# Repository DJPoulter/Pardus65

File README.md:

# Pardus65
Attempting to build a 65% keyboard from scratch

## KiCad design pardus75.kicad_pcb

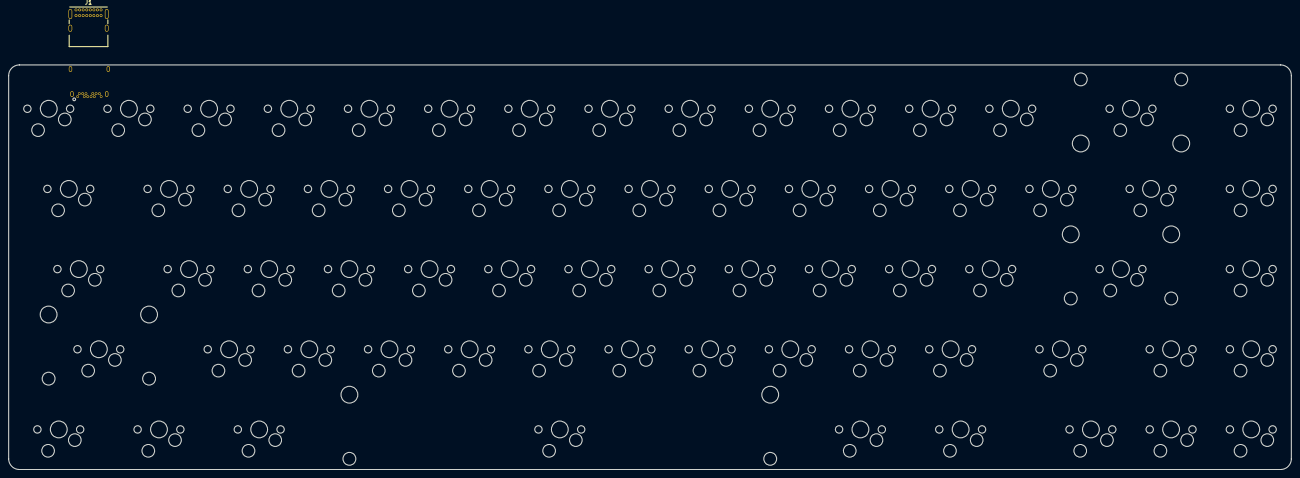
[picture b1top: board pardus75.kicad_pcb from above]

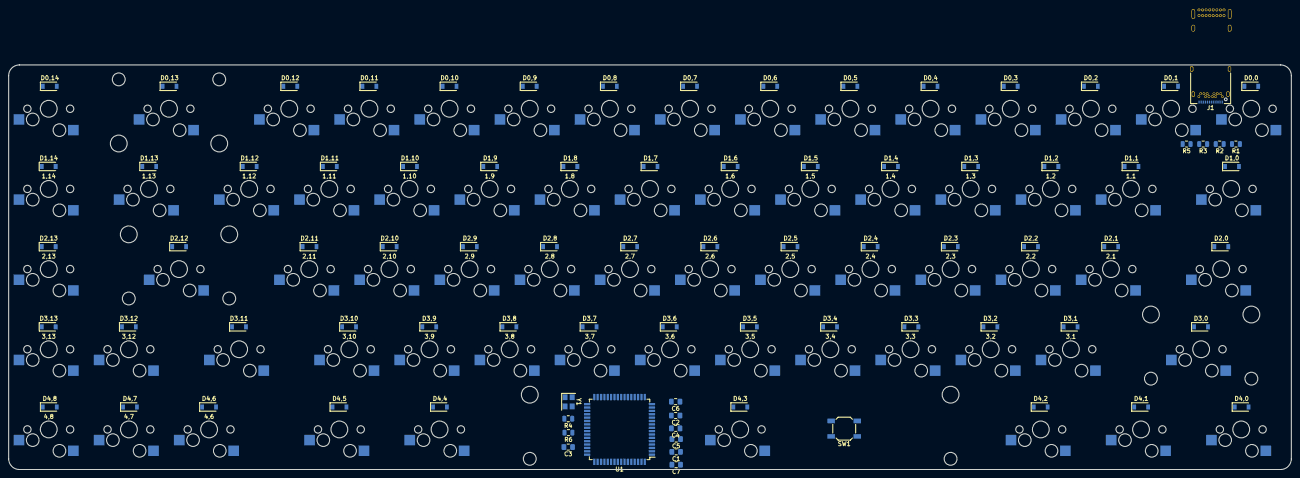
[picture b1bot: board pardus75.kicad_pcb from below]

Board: 2 copper layers, 304.8 x 96.1 mm, 152 parts (85 on the bottom side), 102 nets, no tracks yet.

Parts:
0,0, 0,1, 0,2, 0,3, 0,4, 0,5, 0,6, 0,7, 0,8, 0,9, 0,10, 0,11, 0,12, 0,14, 1,1, 1,2, 1,3, 1,4, 1,5, 1,6, 1,7, 1,8, 1,9, 1,10, 1,11, 1,12, 1,14, 2,1, 2,2, 2,3, 2,4, 2,5, 2,6, 2,7, 2,8, 2,9, 2,10, 2,11, 2,13, 3,1, 3,2, 3,3, 3,4, 3,5, 3,6, 3,7, 3,8, 3,9, 3,10, 3,12, 3,13, 4,6, 4,7, 4,8: MX-NoLED; MXOnly-1U-Hotswap
0,13: MX-NoLED; MXOnly-2U-Hotswap
1,0, 1,13: MX-NoLED; MXOnly-1.5U-Hotswap
2,0, 3,11: MX-NoLED; MXOnly-1.75U-Hotswap
2,12, 3,0: MX-NoLED; MXOnly-2.25U-Hotswap
4,0, 4,1, 4,2, 4,4, 4,5: MX-NoLED; MXOnly-1.25U-Hotswap
4,3: MX-NoLED; MXOnly-6.25U-Hotswap
C1, C4: 1uF; C_0805_2012Metric_Pad1.15x1.40mm_HandSolder
C2, C3: 22pF; C_0805_2012Metric_Pad1.15x1.40mm_HandSolder
C5, C6, C7: 0.1uF; C_0805_2012Metric_Pad1.15x1.40mm_HandSolder
D0,0, D0,1, D0,2, D0,3, D0,4, D0,5, D0,6, D0,7, D0,8, D0,9, D0,10, D0,11, D0,12, D0,13, D0,14, D1,0, D1,1, D1,2, D1,3, D1,4, D1,5, D1,6, D1,7, D1,8, D1,9, D1,10, D1,11, D1,12, D1,13, D1,14, D2,0, D2,1, D2,2, D2,3, D2,4, D2,5, D2,6, D2,7, D2,8, D2,9, D2,10, D2,11, D2,12, D2,13, D3,0, D3,1, D3,2, D3,3, D3,4, D3,5, D3,6, D3,7, D3,8, D3,9, D3,10, D3,11, D3,12, D3,13, D4,0, D4,1, D4,2, D4,3, D4,4, D4,5, D4,6, D4,7, D4,8: D_Small; D_SOD-123
J1: USB4085-GF-A_REVA; USB_C_Receptacle_GCT_USB4085
J1#2: USB_C_Receptacle; USB_C_Receptacle_Amphenol_12401548E4-2A
R1, R2: 5K1; R_0805_2012Metric
R3, R5: 22; R_0805_2012Metric
R4, R6: 10k; R_0805_2012Metric
SW1: SW_Push; SW_SPST_SKQG_WithStem
U1: AT90USB1286-AU; TQFP-64_14x14mm_P0.8mm
Y1: 16MHz; Crystal_SMD_3225-4Pin_3.2x2.5mm

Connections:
+5V: C1.1, C5.1, C6.1, C7.1, J1.A4, J1.A9, J1.B4, J1.B9, J1#2.A4, J1#2.A9, J1#2.B4, J1#2.B9, R6.1, U1.3, U1.8, U1.21, U1.52, U1.64
COL0: 0,0.1, 1,0.1, 2,0.1, 3,0.1, 4,0.1
COL1: 0,1.1, 1,1.1, 2,1.1, 3,1.1, 4,1.1
COL2: 0,2.1, 1,2.1, 2,2.1, 3,2.1, 4,2.1
COL3: 0,3.1, 1,3.1, 2,3.1, 3,3.1
COL4: 0,4.1, 1,4.1, 2,4.1, 3,4.1
COL5: 0,5.1, 1,5.1, 2,5.1, 3,5.1, 4,3.1
COL6: 0,6.1, 1,6.1, 2,6.1, 3,6.1
COL7: 0,7.1, 1,7.1, 2,7.1, 3,7.1
COL8: 0,8.1, 1,8.1, 2,8.1, 3,8.1
COL9: 0,9.1, 1,9.1, 2,9.1, 3,9.1, 4,4.1
COL10: 0,10.1, 1,10.1, 2,10.1, 3,10.1, 4,5.1
COL11: 0,11.1, 1,11.1, 2,11.1, 3,11.1, 4,6.1
COL12: 0,12.1, 1,12.1, 2,12.1, 3,12.1, 4,7.1
COL13: 0,13.1, 1,13.1, 2,13.1, 3,13.1, 4,8.1
COL14: 0,14.1, 1,14.1
D+: J1.A6, J1.B6, J1#2.A6, J1#2.B6, R5.2
D-: J1.A7, J1.B7, J1#2.A7, J1#2.B7, R3.2
GND: C1.2, C2.2, C3.2, C4.2, C5.2, C6.2, C7.2, J1.A1, J1.A12, J1.B1, J1.B12, J1#2.A1, J1#2.A12, J1#2.B1, J1#2.B12, J1#2.S1, R1.2, R2.2, R4.2, SW1.1, U1.6, U1.22, U1.53, U1.63, Y1.2, Y1.4
unnamed: 0,0.2, D0,0.2
unnamed: 0,1.2, D0,1.2
unnamed: 0,2.2, D0,2.2
unnamed: 0,3.2, D0,3.2
unnamed: 0,4.2, D0,4.2
unnamed: 0,5.2, D0,5.2
unnamed: 0,6.2, D0,6.2
unnamed: 0,7.2, D0,7.2
unnamed: 0,8.2, D0,8.2
unnamed: 0,9.2, D0,9.2
unnamed: 0,10.2, D0,10.2
unnamed: 0,11.2, D0,11.2
unnamed: 0,12.2, D0,12.2
unnamed: 0,13.2, D0,13.2
unnamed: 0,14.2, D0,14.2
unnamed: 1,0.2, D1,0.2
unnamed: 1,1.2, D1,1.2
unnamed: 1,2.2, D1,2.2
unnamed: 1,3.2, D1,3.2
unnamed: 1,4.2, D1,4.2
unnamed: 1,5.2, D1,5.2
unnamed: 1,6.2, D1,6.2
unnamed: 1,7.2, D1,7.2
unnamed: 1,8.2, D1,8.2
unnamed: 1,9.2, D1,9.2
unnamed: 1,10.2, D1,10.2
unnamed: 1,11.2, D1,11.2
unnamed: 1,12.2, D1,12.2
unnamed: 1,13.2, D1,13.2
unnamed: 1,14.2, D1,14.2
unnamed: 2,0.2, D2,0.2
unnamed: 2,1.2, D2,1.2
unnamed: 2,2.2, D2,2.2
unnamed: 2,3.2, D2,3.2
unnamed: 2,4.2, D2,4.2
unnamed: 2,5.2, D2,5.2
unnamed: 2,6.2, D2,6.2
unnamed: 2,7.2, D2,7.2
unnamed: 2,8.2, D2,8.2
unnamed: 2,9.2, D2,9.2
unnamed: 2,10.2, D2,10.2
unnamed: 2,11.2, D2,11.2
unnamed: 2,12.2, D2,12.2
unnamed: 2,13.2, D2,13.2
unnamed: 3,0.2, D3,0.2
unnamed: 3,1.2, D3,1.2
unnamed: 3,2.2, D3,2.2
unnamed: 3,3.2, D3,3.2
unnamed: 3,4.2, D3,4.2
unnamed: 3,5.2, D3,5.2
unnamed: 3,6.2, D3,6.2
unnamed: 3,7.2, D3,7.2
unnamed: 3,8.2, D3,8.2
unnamed: 3,9.2, D3,9.2
unnamed: 3,10.2, D3,10.2
unnamed: 3,11.2, D3,11.2
unnamed: 3,12.2, D3,12.2
unnamed: 3,13.2, D3,13.2
unnamed: 4,0.2, D4,0.2
unnamed: 4,1.2, D4,1.2
unnamed: 4,2.2, D4,2.2
unnamed: 4,3.2, D4,3.2
unnamed: 4,4.2, D4,4.2
unnamed: 4,5.2, D4,5.2
unnamed: 4,6.2, D4,6.2
unnamed: 4,7.2, D4,7.2
unnamed: 4,8.2, D4,8.2
unnamed: C2.1, U1.24, Y1.1
unnamed: C3.1, U1.23, Y1.3
unnamed: C4.1, U1.7
unnamed: J1.A5, J1#2.A5, R1.1
unnamed: J1.A8, J1#2.A8
unnamed: J1.B5, J1#2.B5, R2.1
unnamed: J1.B8, J1#2.B8
unnamed: R3.1, U1.4
unnamed: R4.1, U1.43
unnamed: R5.1, U1.5
unnamed: R6.2, SW1.2, U1.20
ROW0: D0,0.1, D0,1.1, D0,2.1, D0,3.1, D0,4.1, D0,5.1, D0,6.1, D0,7.1, D0,8.1, D0,9.1, D0,10.1, D0,11.1, D0,12.1, D0,13.1, D0,14.1
ROW1: D1,0.1, D1,1.1, D1,2.1, D1,3.1, D1,4.1, D1,5.1, D1,6.1, D1,7.1, D1,8.1, D1,9.1, D1,10.1, D1,11.1, D1,12.1, D1,13.1, D1,14.1
ROW2: D2,0.1, D2,1.1, D2,2.1, D2,3.1, D2,4.1, D2,5.1, D2,6.1, D2,7.1, D2,8.1, D2,9.1, D2,10.1, D2,11.1, D2,12.1, D2,13.1
ROW3: D3,0.1, D3,1.1, D3,2.1, D3,3.1, D3,4.1, D3,5.1, D3,6.1, D3,7.1, D3,8.1, D3,9.1, D3,10.1, D3,11.1, D3,12.1, D3,13.1
ROW4: D4,0.1, D4,1.1, D4,2.1, D4,3.1, D4,4.1, D4,5.1, D4,6.1, D4,7.1, D4,8.1

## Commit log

2020-08-22 Adding dummy pcb
2020-08-22 Add submodules
2020-08-22 linking libraries
2020-08-22 Adding MCU and USBC
2020-08-23 PCB added
2020-09-03 Adding USBC
2020-09-03 TypeC
